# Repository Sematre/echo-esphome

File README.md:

# Echo ESPHome
> [!NOTE] 
> :construction: This project is WIP. :construction:

Home Assistant compatible voice assistant, with on-device voice activation, mainboard drop-in replacement for Amazon Echo Dot (2nd Gen).

## Echo Dot (2nd Gen) Hardware
### Top board
- 4x ADC with miniDSP: [TLV320ADC3101](https://www.ti.com/product/de-de/TLV320ADC3101) ([Datasheet](https://www.ti.com/lit/ds/symlink/tlv320adc3101.pdf))
    - Each chip is connected to 2 stereo microphones
- 7x Microphone (6 ring + 1 center)
- 1x 36-Channel LED driver: [IS31FL3236A](https://www.lumissil.com/applications/industrial/appliance/major-appliances/range-hood/is31fl3236a) ([Datasheet](https://www.lumissil.com/assets/pdf/core/IS31FL3236A_DS.pdf))
- 12x RGBW LED
- 4x Tacktile dom switch
    - 1x Red LED on mute button
    - 1x Light sensor on action button
- 1x Tri-state buffer: [74LVC1G125](https://www.diodes.com/assets/Datasheets/74LVC1G125.pdf)

### Mainboard
- 1x Class-D stereo speaker amplifier: [TPA3118D2](https://www.ti.com/product/TPA3118D2) ([Datasheet](https://www.ti.com/lit/ds/symlink/tpa3118d2.pdf))

## Getting started
```sh
$ git clone --recurse-submodules https://github.com/Sematre/echo-esphome.git
```

## Resources
- [Retasking a 2nd Gen Echo](https://community.home-assistant.io/t/retasking-a-2nd-gen-echo/709084) *by Terry Sanders*
- [Inside the Amazon Echo Dot (3rd Gen): A Complete Teardown](https://pallavaggarwal.in/2023/01/10/teardown-amazon-echo-dot-3rd-gen/) *by Pallav Aggarwal*

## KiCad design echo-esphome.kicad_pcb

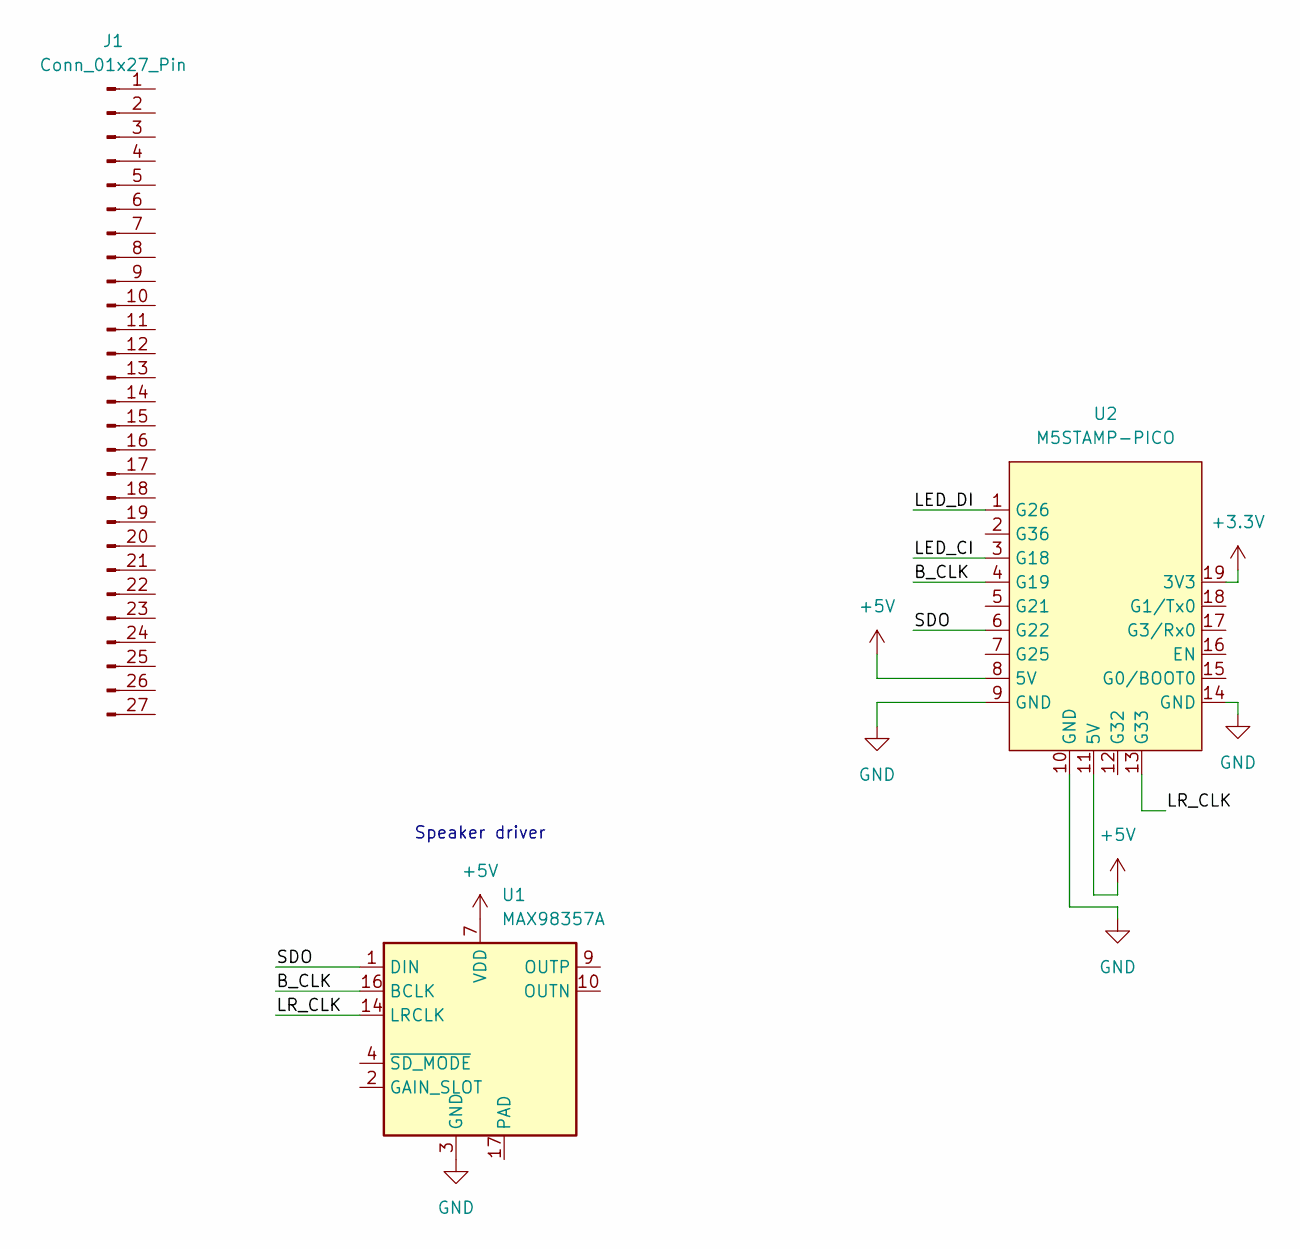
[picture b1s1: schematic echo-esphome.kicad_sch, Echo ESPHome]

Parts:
J1: Conn_01x27_Pin; Hirose_FH26-27S-0.3SHW_2Rows-27Pins-1MP_P0.60mm_Horizontal
U1: MAX98357A; TQFN-16-1EP_3x3mm_P0.5mm_EP1.23x1.23mm
U2: M5STAMP-PICO

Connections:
+3.3V: U2.19 (3V3)
+5V: U1.7 (VDD), U1.8 (VDD), U2.8 (5V), U2.11 (5V)
/B_CLK: U1.16 (BCLK), U2.4 (G19)
/LED_CI: U2.3 (G18)
/LED_DI: U2.1 (G26)
/LR_CLK: U1.14 (LRCLK), U2.13 (G33)
/SDO: U1.1 (DIN), U2.6 (G22)
GND: U1.3 (GND), U1.11 (GND), U1.15 (GND), U2.9 (GND), U2.10 (GND), U2.14 (GND)

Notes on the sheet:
Speaker driver

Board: 2 copper layers, 3 parts (0 on the bottom side), 5 nets, no tracks yet.

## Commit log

2024-09-03 Documentation and basic board layout
2024-09-03 Project notice
2024-09-03 Getting started guilde
2024-09-03 Fix chip nr
2024-09-03 Fix wording
2024-09-03 Add ci
2024-09-03 Add measurements
2024-09-03 Fix ci path
2024-09-04 ci: Add trigger condition
2024-09-07 Update deps in ci
2025-05-14 Create drc heatmap
2025-05-14 Change ci name
